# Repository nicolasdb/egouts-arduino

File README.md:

# MUSEE DES EGOUTS
Une maquette sur le cycle anthropique de l'eau et ses supports didactiques  
Projet Arduino pour l'automatisation des écoulements d'eau.   

## Appel à projet remporté par:

**Ignacio Plaza De Giles** : architecte, maquettiste  
_Conception et réalisation + modelisation 3D, impression 3D, découpe laser_  
**Nicolas de Barquin** : co-fondateur de OpenFab  
_Conception et réalisation + support technique sur le design et l'électronique_  
**Juan Vandeput** : menuisier, ébéniste  
_Conception et réalisation + construction bois_  
**Alexandra Sebbag** : graphiste  
_Conception et réalisation des jeux + design et légendes de la maquette_  
**Hélène Mariage** : paysagiste, maquettiste  
_Conception et réalisation + communication, logistique_  

## License

This project is licensed under the GNU General Public License v3.0 - see the [LICENSE](LICENSE) file for details.

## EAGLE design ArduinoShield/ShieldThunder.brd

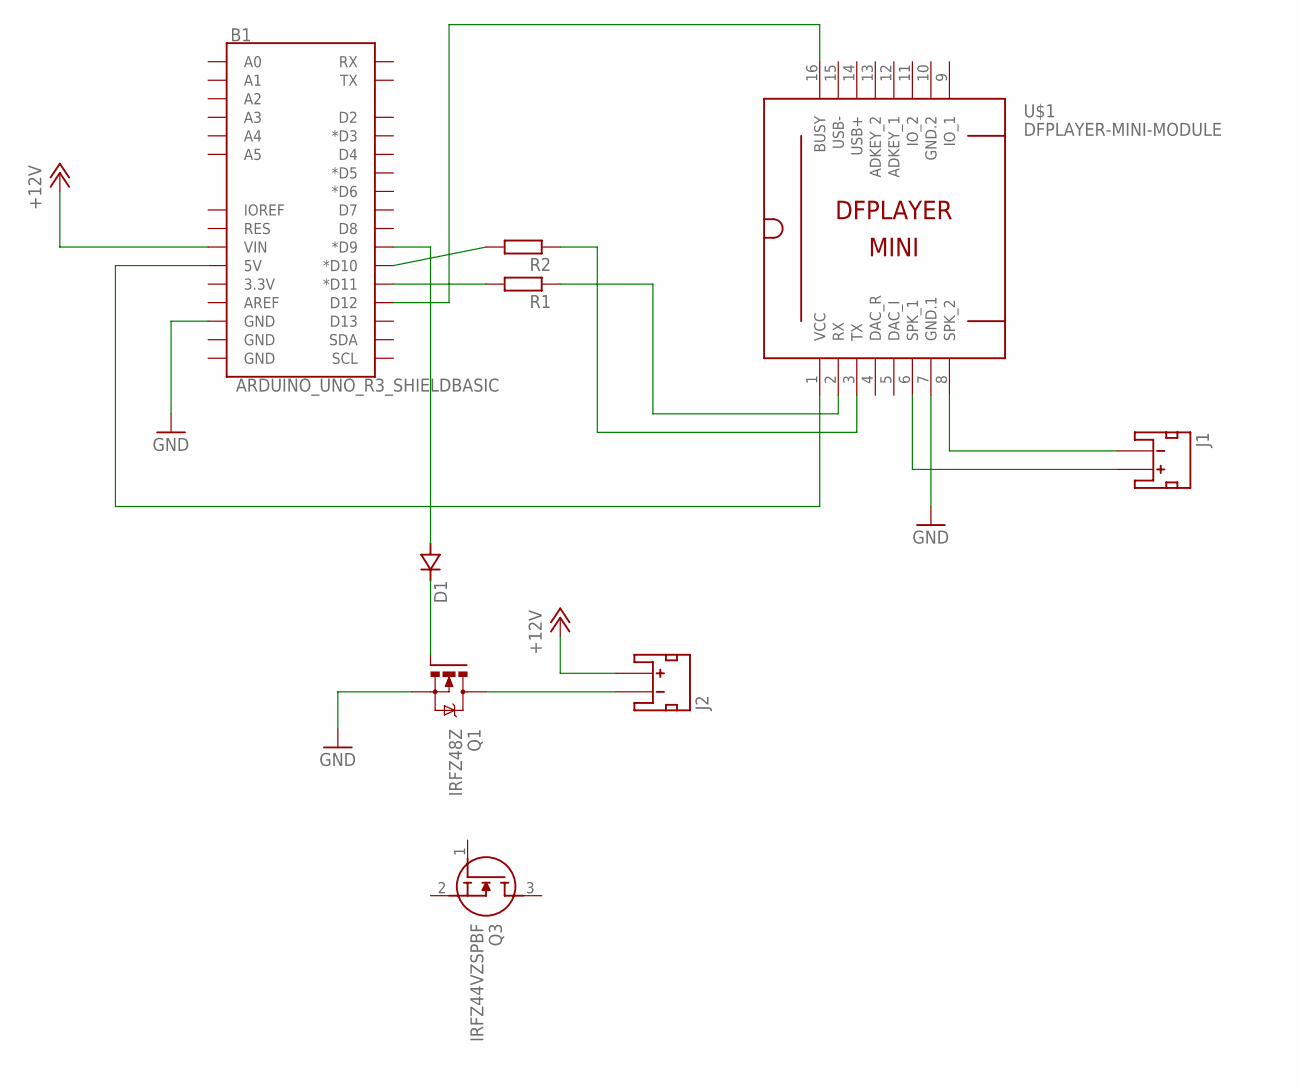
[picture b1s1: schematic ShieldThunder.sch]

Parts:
B1: ARDUINO_UNO_R3_SHIELDBASIC; UNO_R3_SHIELD
D1: DSOT23; SOT-23
J1, J2: JST_2MM_MALE; JST-2-SMD
Q1: IRFZ48Z; TO220BH
Q3: IRFZ44VZSPBF; D2PAK(TO-263AB)
R1, R2: R-EU_R0805; R0805
U$1: DFPLAYER-MINI-MODULE

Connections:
+12V: B1.VIN, J2.2 (+)
GND: B1.GND@2 (GND), Q1.S, U$1.7 (GND.1)
GND.2: U$1.10 (GND.2)
unnamed: B1.D10 (*D10), R2.2
unnamed: B1.D11 (*D11), R1.2
unnamed: R1.1, U$1.2 (RX)
unnamed: R2.1, U$1.3 (TX)
unnamed: B1.D12, U$1.16 (BUSY)
unnamed: J1.2 (+), U$1.6 (SPK_1)
unnamed: J1.1 (-), U$1.8 (SPK_2)
unnamed: B1.D9 (*D9), D1.3 (A)
unnamed: D1.1 (C), Q1.G
unnamed: J2.1 (-), Q1.D
unnamed: B1.5V, U$1.1 (VCC)

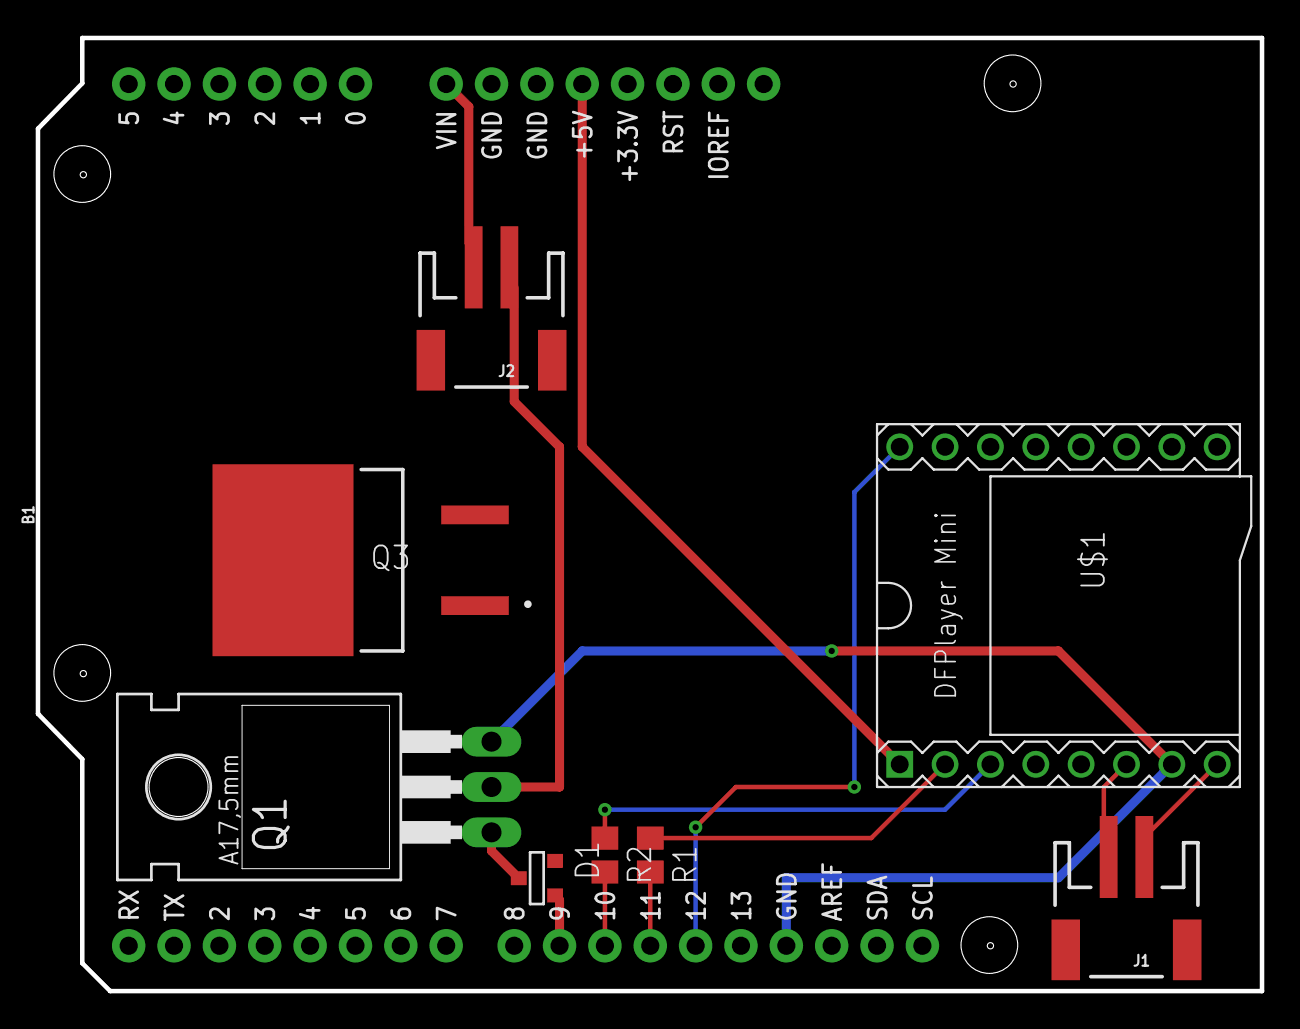
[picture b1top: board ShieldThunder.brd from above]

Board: 2 copper layers, 68.5 x 53.4 mm, 9 parts (0 on the bottom side), 13 nets.

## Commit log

2019-06-20 init(egouts): initial commit
2019-06-20 fix(freetos): add in lib_deps
2019-06-20 feat(mp3): add fake mp3
2019-06-21 add fade and start on mp3
    fade = juste un blink commun des pins 345
    le vrai fade viendra plus tard.
2019-06-21 bug in mp3
    error: '*****' was not declared in this scope
    a lot
2019-06-24 it's working
    with just 3 buttons and thunder mp3
2019-06-25 add MCP
    ça marche plus.
    FreeRTOS cassé
2019-06-25 yeah ça remarche
    Idle ok,
    Boutons ok.
    LedsBoutons ok,
    mp3 ok,
2019-06-26 update 9 scenarios
    + init EagleBoard
2019-07-03 start actions
2019-07-03 init shield
    error from branching...
2019-07-04 new update, mcp 1 et 2
2019-07-05 fine tune sur schem and delays
    getting down to 7 buttons,
    I set a 8th on hardware, just in case
2019-07-05 add mp3, mcp1 et 2 and pumplevel
2019-07-05 end v1 schemboard
2019-07-05 fail, pump task
    the rest is ok, sort of.
2019-07-05 add comment for input
2019-07-06 pump still not working
2019-07-08 passage sur shield
    que les boutons.
    Réordonne les num et leds boutons
2019-07-08 add mp3 on shield
2019-07-09 add relais 0-16
2019-07-11 add arduino on shield
    and some stuffs
2019-07-12 delete mcp2, add leds controls
    assez de pins sur arduino pour les quelques leds qui restent à controler.
2019-07-12 last leds control, shield completed
    Version1, hopeSO
2019-08-21 cleaning and update for test IRL
    still no pump action
2019-08-22 add function to play specific mp3
2019-08-22 update list valves
2019-08-23 ajout pistes sons et prepa valves
2019-08-28 change to 2N4401 and connection to VSS
2019-08-30 mise à jour des valves
2019-09-03 last test, still a bug with IDLE LEDs
2019-09-03 mise à jour scenario + debug hardware
2019-09-04 last scenario
2019-09-12 correction suite à la remise
2020-06-16 update timing scénario
    attention à la mise à jour freeRTOS qui fait buger la syntaxe. use FreeRTOS 10.1.1-1
2022-05-23 no change, but new error from freeRTOS solved
2022-06-04 start debug before production pcb
2022-06-04 LED button + mp3 resolved, carte SD was broken
2022-06-05 Button nearley ready
2022-06-06 identification des boutons, problème selon power sup.
2022-06-11 mise à jour photos
2022-06-14 Mise à jour board design avec easyEDA
2022-06-14 add delay for mp3
2022-06-18 cleaning and nano init ok
2022-07-04 PCB fully checked and corrected
2022-07-05 Add mp3 sources
2022-07-05 cases validé et système en place
2022-08-10 last update before install
2024-08-12 update ini nano and lib mcp
2024-09-14 Adjustment to new set of valves
2024-09-16 24.09 update nano and readme
2024-09-18 init diagnostic branch
2024-09-18 running without scenario or freertos
2024-09-18 working but need adjustement on scenarios
2024-09-18 update scenarios based on backup
2024-09-18 problem solved
2025-12-27 improvement plan with valve_module concept
2026-02-18 add cycle eau map

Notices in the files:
parts and their libraries:
SparkFun-Boards: Licensing: Creative Commons ShareAlike 4.0 International - https://creativecommons.org/licenses/by-sa/4.0
diy-modules: Released under the Creative Commons Attribution 4.0 International License: http://creativecommons.org/licenses/by/4.0
